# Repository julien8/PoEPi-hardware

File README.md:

## Raspberry Pi Zero - PoEPi

The Raspberry Pi Zero is a low power and low footprint Raspberry Pi. It gives people an opportunity to move towards compact connected devices
while moving away from being a just a small computer. PiPoE adds a new way of connecting the Raspberry Pi Zero with the world in a very efficient
manner. Power over Ethernet is a way if injecting power into an Ethernet cable without interfering with the data. What it gives you is a high 
reliability way of powering and communicating with the Raspberry Pi. The design of PoEPi is open source under the CERN OHL V1.2 and can be easily
adapted to your own custom designs. 

For more information check out the Wiki on github

### Basic Hardware usage

1. Setup your Raspberry Pi with a monitor and enable SSH with raspi-config
2. Plug Ethernet cable into a PoE switch or add a PoE injector somehwhere in you Ethernet line
3. Connect the PoEPi to the Raspberry Pi
4. Plug in the "injected" Ethernet cable
5. The Pi Zero should be powered and you then SSH into the Pi

For information on the particular PoEPi modules and how to control them please see the wiki on the github page

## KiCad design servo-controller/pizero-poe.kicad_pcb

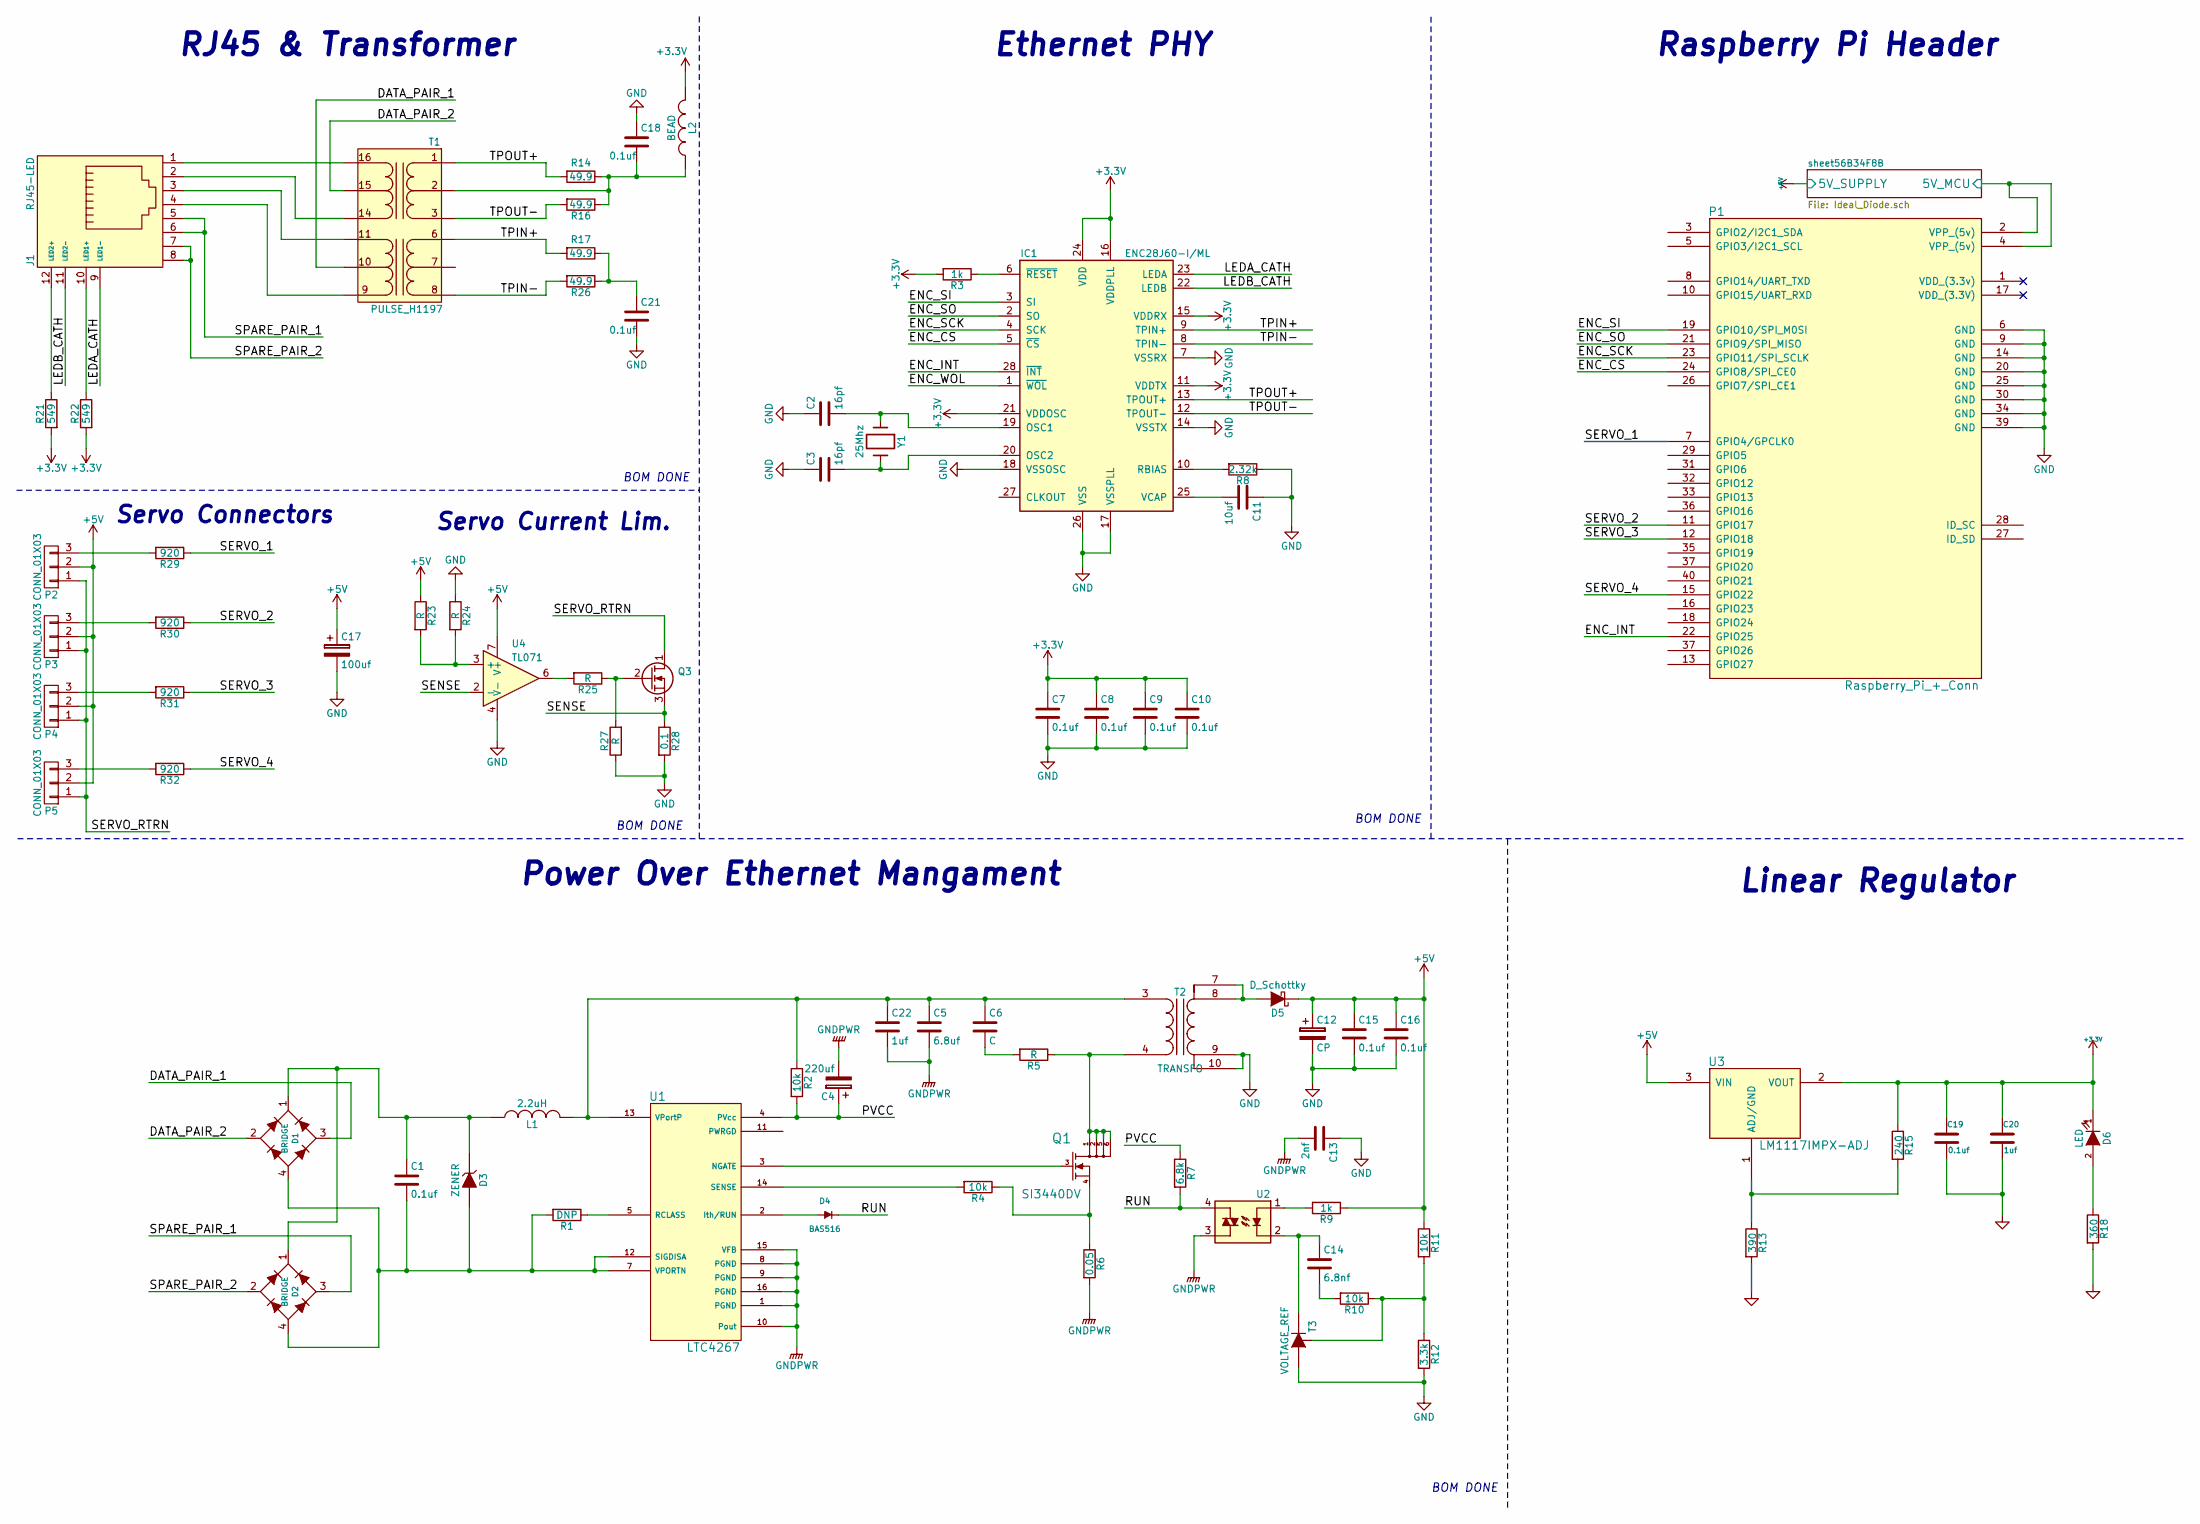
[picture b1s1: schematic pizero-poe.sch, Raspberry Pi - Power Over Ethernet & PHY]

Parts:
C1, C7, C8, C9, C18, C19, C21: 0.1uf; c_0402; Mouser Part No. 710-885012105001
C2, C3: 16pf; c_0402; Mouser Part No. 81-GRM1555C1H160JA1D
C4: 220uf; c_tant_B; Mouser Part No. 581-TAJB475K025R
C5: 6.8uf; c_tant_D; Mouser Part No. 74-293D685X9050D2TE3
C6: C; c_0402
C10, C15, C16: 0.1uf; c_0603; Mouser Part No. 710-885012105001
C11: 10uf; c_0603; Mouser Part No. 81-ZRB18AR61C106ME1L
C12: CP; c_elec_4x4.5; Mouser Part No. 667-EEE-1AA330WR
C13: 2nf; c_0603; Mouser Part No. 81-GRM1885C1H202JA1D
C14: 6.8nf; c_0402; Mouser Part No. 81-GRM155R71H682KA8D
C17: 100uf; c_elec_8x6.5
C20: 1uf; c_0402; Mouser Part No. 810-C1005X5R1H104K
C22: 1uf; c_0805; Mouser Part No. 810-C2012X7S2A105K
D1, D2: BRIDGE; MBS; Mouser Part No. 621-HD01-T
D3: ZENER; do214ac; Mouser Part No. 576-SMAJ58A
D4: BAS516; sod523; Mouser Part No. 771-BAS516-T/R
D5: D_Schottky; do214ab; Mouser Part No. 621-B360A-F
D6: LED; Led_0603; Mouser Part No. 743-HT-191USD
IC1: ENC28J60-I/ML; qfn-28; Mouser Part No. 579-ENC28J60-I/ML
J1: RJ45-LED; rj45-tyco-2-406549-7; Mouser Part No. 710-615008137421
L1: 2.2uH; inductor_smd_1008; Mouser Part No. 81-LQM2HPN2R2MEHL
L2: BEAD; inductor_smd_0402; Mouser Part No. 81-BLM15AG102SN1D
P1: Raspberry_Pi_+_Conn
P2, P3, P4, P5: CONN_01X03; pin_strip_3
Q1: SI3440DV; tsot-6; Mouser Part No. 781-SI3440DV-E3
Q3: Q_NMOS_DGS; d-pak
R1: DNP; r_0402
R2, R4, R10, R11: 10k; r_0402; Mouser Part No. 754-RR0510P-103D
R3: 1k; r_0402; Mouser Part No. 754-RR0510P-102D
R5, R23, R24, R25, R27: R; r_0402
R6: 0.05; r_1206; Mouser Part No. 660-UR732BTTD50L0F
R7: 6.8k; r_0402; Mouser Part No. 754-RR0510P-682D
R8: 2.32k; r_0402; Mouser Part No. 667-ERJ-2RKF2321X
R9: 1k; r_0402
R12: 3.3k; r_0402; Mouser Part No. 754-RR0510P-332D
R13: 390; r_0402; Mouser Part No. 594-MCT06030C3900FP5
R14, R16, R17, R26: 49.9; r_0402; Mouser Part No. 660-RK73H1ETQTP49R9F
R15: 240; r_0402; Mouser Part No. 754-RR0816P-241D
R18: 360; r_0402; Mouser Part No. 71-CRCW0603316RFKEB
R21, R22: 549; r_0402; Mouser Part No. 667-ERJ-2RKF5490X
R28: 0.1; r_1210
R29, R30, R31, R32: 920; r_0402
T1: PULSE_H1197; H2019; Mouser Part No. 673-H1197FNL
T2: TRANSFO; PoE_TRANS; Mouser Part No. 710-7491199501
T3: VOLTAGE_REF; sot23; Mouser Part No. 863-TLV431BSN1T1G
U1: LTC4267; ssop-16; Digikey Part No. LTC4267CGN-3#PBF-ND
U2: PAS291; OPTO_ISO; Mouser Part No. 551-PS2911-1-K-AX
U3: LM1117IMPX-ADJ; sot223; Mouser Part No. 926-M1117IMPXADJNOPB
U4: TL071; so-8
Y1: 25Mhz; crystal_smd_5x3.2mm; Mouser Part No. 774-445I23D25M00000

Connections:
+3V3: C7.1, C8.1, C9.1, C10.1, C19.1, C20.1, D6.1 (K), IC1.11 (VDDTX), IC1.15 (VDDRX), IC1.16 (VDDPLL), IC1.21 (VDDOSC), IC1.24 (VDD), L2.2, R3.2, R15.1, R21.2, R22.2, U3.2 (VOUT)
+5V: C12.1, C15.1, C16.1, C17.1, D5.1 (K), P2.2, P3.2, P4.2, P5.2, R9.1, R11.1, R23.1, U3.3 (VIN), U4.7 (V+); also elsewhere on the board
/DATA_PAIR_1: D1.3 (~2), T1.10
/DATA_PAIR_2: D1.2 (~1), T1.15
/ENC_CS: IC1.5 (~CS), P1.24 (GPIO8/SPI_CE0)
/ENC_INT: IC1.28 (~INT), P1.22 (GPIO25)
/ENC_SCK: IC1.4 (SCK), P1.23 (GPIO11/SPI_SCLK)
/ENC_SI: IC1.3 (SI), P1.19 (GPIO10/SPI_M0SI)
/ENC_SO: IC1.2 (SO), P1.21 (GPIO9/SPI_MISO)
/ENC_WOL: IC1.1 (~WOL)
/LEDA_CATH: IC1.23 (LEDA), J1.9 (LED1-)
/LEDB_CATH: IC1.22 (LEDB), J1.11 (LED2-)
/PVCC: C4.1, R2.2, R7.1, U1.4 (PVcc)
/RUN: D4.2 (K), R7.2, U2.4
/SENSE: Q3.3 (S), R28.1, U4.2 (-)
/SERVO_1: P1.7 (GPIO4/GPCLK0), R29.1
/SERVO_2: P1.11 (GPIO17), R30.1
/SERVO_3: P1.12 (GPIO18), R31.1
/SERVO_4: P1.15 (GPIO22), R32.1
/SERVO_RTRN: P2.1, P3.1, P4.1, P5.1, Q3.1 (D)
/SPARE_PAIR_1: D2.3 (~2), J1.5, J1.6
/SPARE_PAIR_2: D2.2 (~1), J1.7, J1.8
/TPIN+: IC1.9 (TPIN+), R17.2, T1.6 (PR1)
/TPIN-: IC1.8 (TPIN-), R26.2, T1.8 (PR2)
/TPOUT+: IC1.13 (TPOUT+), R14.2, T1.1 (PR1)
/TPOUT-: IC1.12 (TPOUT-), R16.2, T1.3 (PR2)
/sheet56B34F8B/5V_MCU: P1.2 (VPP_(5v)), P1.4 (VPP_(5v)); also elsewhere on the board
GND: C2.1, C3.1, C7.2, C8.2, C9.2, C10.2, C11.1, C12.2, C13.1, C15.2, C16.2, C17.2, C18.1, C19.2, C20.2, C21.2, IC1.7 (VSSRX), IC1.14 (VSSTX), IC1.17 (VSSPLL), IC1.18 (VSSOSC), IC1.26 (VSS), P1.6 (GND), P1.9 (GND), P1.14 (GND), P1.20 (GND), P1.25 (GND), P1.30 (GND), P1.34 (GND), P1.39 (GND), R8.1, R12.2, R13.2, R18.2, R24.1, R27.1, R28.2, T2.9 (SA), T2.10, T3.2 (A), U4.4 (V-); also elsewhere on the board
GNDPWR: C4.2, C5.2, C13.2, C22.2, R6.2, U1.1 (PGND), U1.8 (PGND), U1.9 (PGND), U1.10 (Pout), U1.15 (VFB), U1.16 (PGND), U2.3
unnamed: C1.1, D1.1 (V+), D2.1 (V+), D3.1 (K), L1.1
unnamed: C1.2, D1.4 (V-), D2.4 (V-), D3.2 (A), R1.2, U1.7 (VPORTN), U1.12 (SIGDISA)
unnamed: C2.2, IC1.19 (OSC1), Y1.1
unnamed: C3.2, IC1.20 (OSC2), Y1.2
unnamed: C6.2, R5.2
unnamed: C11.2, IC1.25 (VCAP)
unnamed: C14.1, T3.3 (K), U2.2
unnamed: C14.2, R10.2
unnamed: C18.2, L2.1, R14.1, R16.1, T1.2 (PM)
unnamed: C21.1, R17.1, R26.1
unnamed: C5.1, C6.1, C22.1, L1.2, R2.1, T2.3 (AA), U1.13 (VPortP)
unnamed: D4.1 (A), U1.2 (Ith/RUN)
unnamed: D5.2 (A), T2.7, T2.8 (SB)
unnamed: D6.2 (A), R18.1
unnamed: IC1.6 (~RESET), R3.1
unnamed: IC1.10 (RBIAS), R8.2
unnamed: J1.1, T1.16 (S2)
unnamed: J1.2, T1.14 (S1)
unnamed: J1.3, T1.11 (S2)
unnamed: J1.4, T1.9 (S1)
unnamed: J1.10 (LED1+), R22.1
unnamed: J1.12 (LED2+), R21.1
unnamed: P2.3, R29.2
unnamed: P3.3, R30.2
unnamed: P4.3, R31.2
unnamed: P5.3, R32.2
unnamed: Q1.1 (D), Q1.2 (D), Q1.5 (D), Q1.6 (D), R5.1, T2.4 (AB)
unnamed: Q1.3 (G), U1.3 (NGATE)
unnamed: Q1.4 (S), R4.1, R6.1
unnamed: Q3.2 (G), R25.1, R27.2
unnamed: R1.1, U1.5 (RCLASS)
unnamed: R4.2, U1.14 (SENSE)
unnamed: R9.2, U2.1
unnamed: R10.1, R11.2, R12.1, T3.1 (G)
unnamed: R13.1, R15.2, U3.1 (ADJ/GND)
unnamed: R23.2, R24.2, U4.3 (+)
unnamed: R25.2, U4.6

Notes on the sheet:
Linear Regulator
Power Over Ethernet Mangament
RJ45 & Transformer
Ethernet PHY
Raspberry Pi Header
BOM DONE
Servo Connectors
Servo Current Lim.

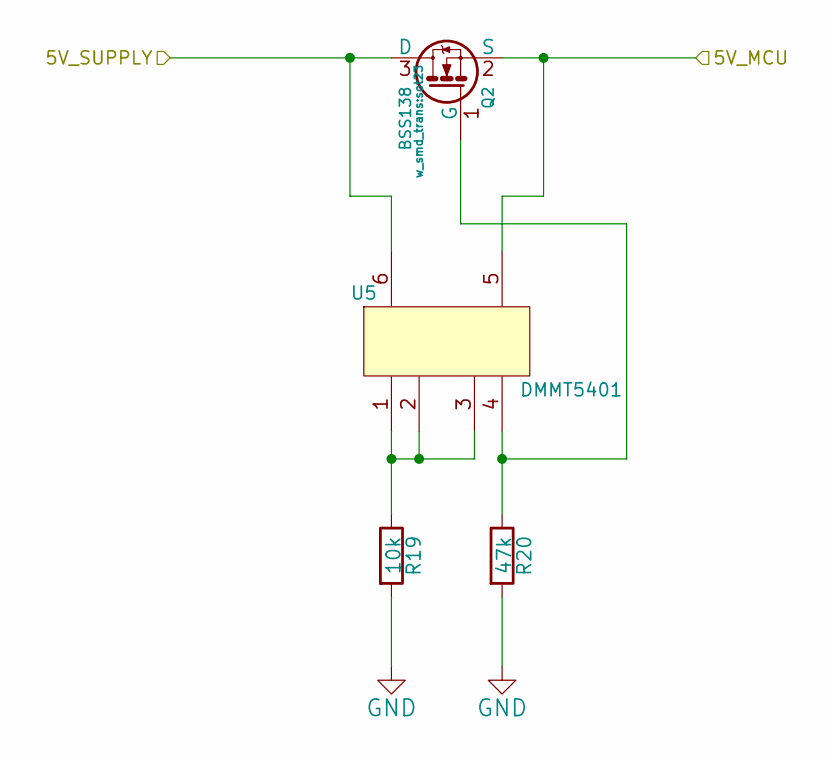
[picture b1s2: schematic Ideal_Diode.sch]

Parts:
Q2: BSS138; sot23; Mouser Part No. 621-DMG2305UX-13
R19: 10k; r_0402; Mouser Part No. 71-CRCW0402-10K-E3
R20: 47k; r_0402; Mouser Part No. 667-ERJ-2RKF4702X
U5: DMMT5401; sot23-6; Mouser Part No. 621-DMMT5401-7-F

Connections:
+5V: Q2.3 (D), U5.6; also elsewhere on the board
/sheet56B34F8B/5V_MCU: Q2.2 (S), U5.5; also elsewhere on the board
GND: R19.2, R20.2; also elsewhere on the board
unnamed: Q2.1 (G), R20.1, U5.4
unnamed: R19.1, U5.1, U5.2, U5.3

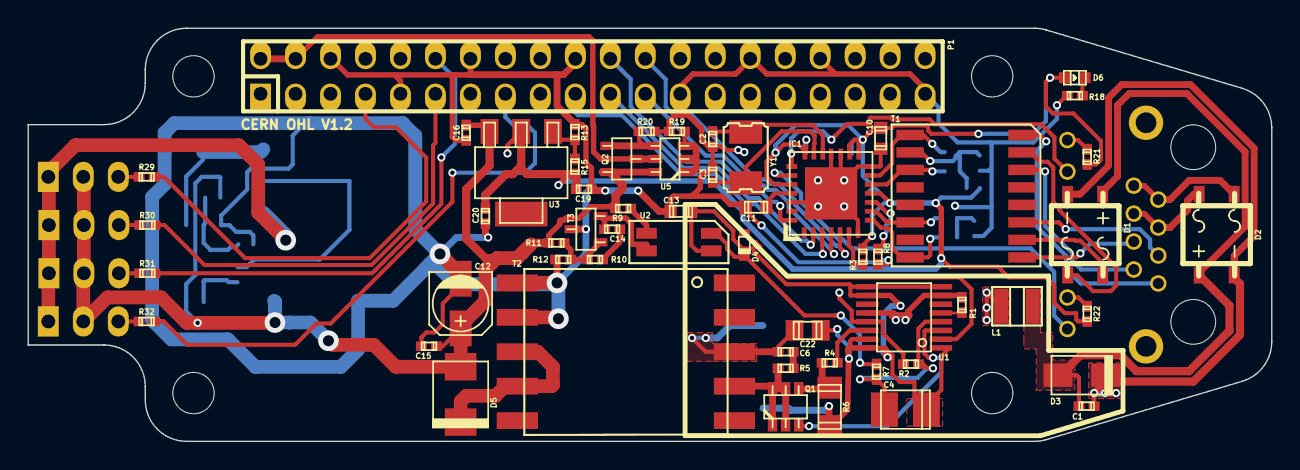
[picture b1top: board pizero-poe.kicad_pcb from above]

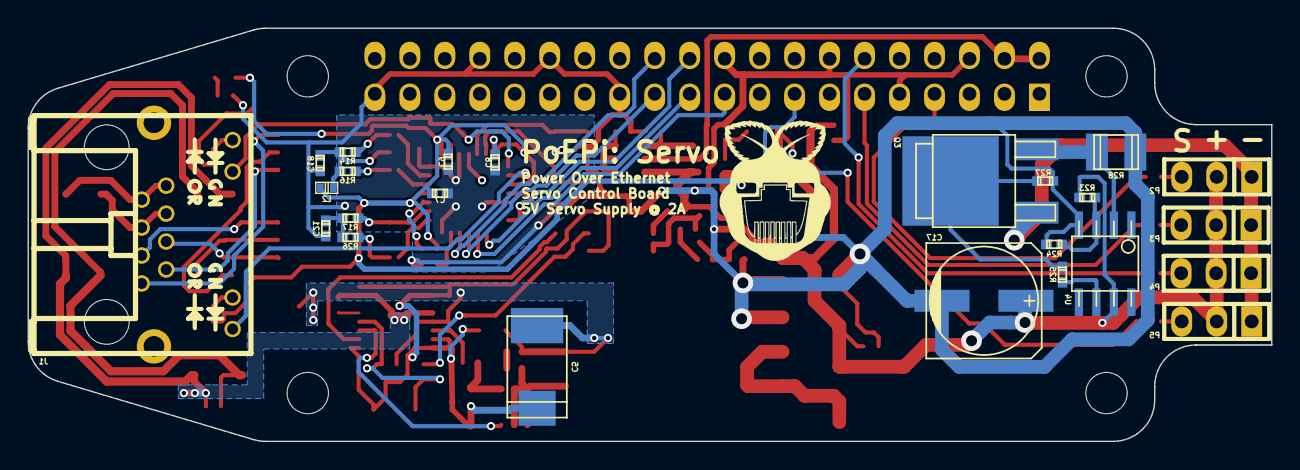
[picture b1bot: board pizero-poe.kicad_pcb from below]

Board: 2 copper layers, 90.3 x 30.0 mm, 85 parts (24 on the bottom side), 67 nets.

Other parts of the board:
MT1, MT2, MT3, MT4: MountingHole_3mm

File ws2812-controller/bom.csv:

ref,value,footprint,Mouser Part No.,Quantity
C1 C7 C8 C9 C10 C19 C18 C21 C15 C16,0.1uf,w_smd_cap:c_0402,710-885012105001,10
C11,10uf,w_smd_cap:c_0603,81-ZRB18AR61C106ME1L,1
C12,CP,w_smd_cap:c_elec_4x4.5,667-EEE-1AA330WR,1
C13,2nf,w_smd_cap:c_0603,81-GRM1885C1H202JA1D,1
C14,6.8nf,w_smd_cap:c_0402,81-GRM155R71H682KA8D,1
C17,CP,w_smd_cap:c_elec_8x6.5,667-EEE-1AA221P,1
C2 C3,16pf,w_smd_cap:c_0402,81-GRM1555C1H160JA1D,2
C20,1uf,w_smd_cap:c_0402,810-C1005X5R1H104K,1
C22,1uf,w_smd_cap:c_0805,810-C2012X7S2A105K,1
C4,220uf,w_smd_cap:c_tant_B,581-TAJB475K025R,1
C5,6.8uf,w_smd_cap:c_tant_D,74-293D685X9050D2TE3,1
D1 D2,BRIDGE,w_smd_diode:MBS,621-HD01-T,2
D3,ZENER,w_smd_diode:do214ac,576-SMAJ58A,1
D4,BAS516,w_smd_diode:sod523,771-BAS516-T/R,1
D5,D_Schottky,w_smd_diode:do214ab,621-B360A-F,1
D6,LED,w_smd_leds:Led_0603,743-HT-191USD,1
D7,ZENER,w_smd_diode:sod123,771-BZT52HB5V1115,1
IC1,ENC28J60-I/ML,w_smd_qfn:qfn-28,579-ENC28J60-I/ML,1
J1,RJ45-LED,w_conn_pc:rj45-tyco-2-406549-7,710-615008137421,1
L1,2.2uH,w_smd_inductors:inductor_smd_1008,81-LQM2HPN2R2MEHL,1
L2,BEAD,w_smd_inductors:inductor_smd_0402,81-BLM15AG102SN1D,1
Q1,SI3440DV,w_smd_trans:tsot-6,781-SI3440DV-E3,1
Q2,BSS138,w_smd_trans:sot23,621-DMG2305UX-13,1
Q3,BSS138,w_smd_trans:sot23,512-BSS138,1
R12,3.3k,w_smd_resistors:r_0402,754-RR0510P-332D,1
R13,390,w_smd_resistors:r_0402,594-MCT06030C3900FP5,1
R14 R16 R17 R26,49.9,w_smd_resistors:r_0402,660-RK73H1ETQTP49R9F,4
R15,240,w_smd_resistors:r_0402,754-RR0816P-241D,1
R18,360,w_smd_resistors:r_0402,71-CRCW0603316RFKEB,1
R19,10k,w_smd_resistors:r_0402,71-CRCW0402-10K-E3,1
R2 R4 R10 R11,10k,w_smd_resistors:r_0402,754-RR0510P-103D,4
R20,47k,w_smd_resistors:r_0402,667-ERJ-2RKF4702X,1
R21 R22,549,w_smd_resistors:r_0402,667-ERJ-2RKF5490X,2
R24 R23,14k,w_smd_resistors:r_0402,667-ERJ-2RKF1402X,2
R25,100,w_smd_resistors:r_0402,71-CRCW0402-100-E3,1
R3,1k,w_smd_resistors:r_0402,754-RR0510P-102D,1
R6,0.05,w_smd_resistors:r_1206,660-UR732BTTD50L0F,1
R7,6.8k,w_smd_resistors:r_0402,754-RR0510P-682D,1
R8,2.32k,w_smd_resistors:r_0402,667-ERJ-2RKF2321X,1
T1,PULSE_H1197,project_foot:H2019,673-H1197FNL,1
T2,TRANSFO,project_foot:PoE_TRANS,710-7491199501,1
T3,VOLTAGE_REF,w_smd_trans:sot23,863-TLV431BSN1T1G,1
U2,PAS291,project_foot:OPTO_ISO,551-PS2911-1-K-AX,1
U3,LM1117IMPX-ADJ,w_smd_trans:sot223,926-M1117IMPXADJNOPB,1
U5,DMMT5401,w_smd_trans:sot23-6,621-DMMT5401-7-F,1
Y1,25Mhz,w_crystal:crystal_smd_5x3.2mm,774-445I23D25M00000,1

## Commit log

2016-02-10 Intial commit of PoEPi
2016-02-11 changed cap size, wrong value
2016-02-11 added half of component part numbers
2016-02-11 added EMI filtering on data lines
2016-02-11 added EMI components after update
2016-02-11 changed caps after reviewing notes
2016-02-11 first complete development revision
2016-02-16 initial commit of amplifier
2016-02-23 initial commit of servo board

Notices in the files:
servo-controller/pizero-poe.kicad_pcb:
License: CERN OHL V1.2
